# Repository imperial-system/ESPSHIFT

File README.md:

# ESP8266 8 RELAY
 ESPSHIFT es una placa DIY diseñada para el Internet Of Things, cuenta con 8 relays y fuente de alimentación propia. Esta basado en el ESP01 que resulta barato y facil para removerlo y programarlo de forma externa. 
 El proyecto esta realizado en kicad

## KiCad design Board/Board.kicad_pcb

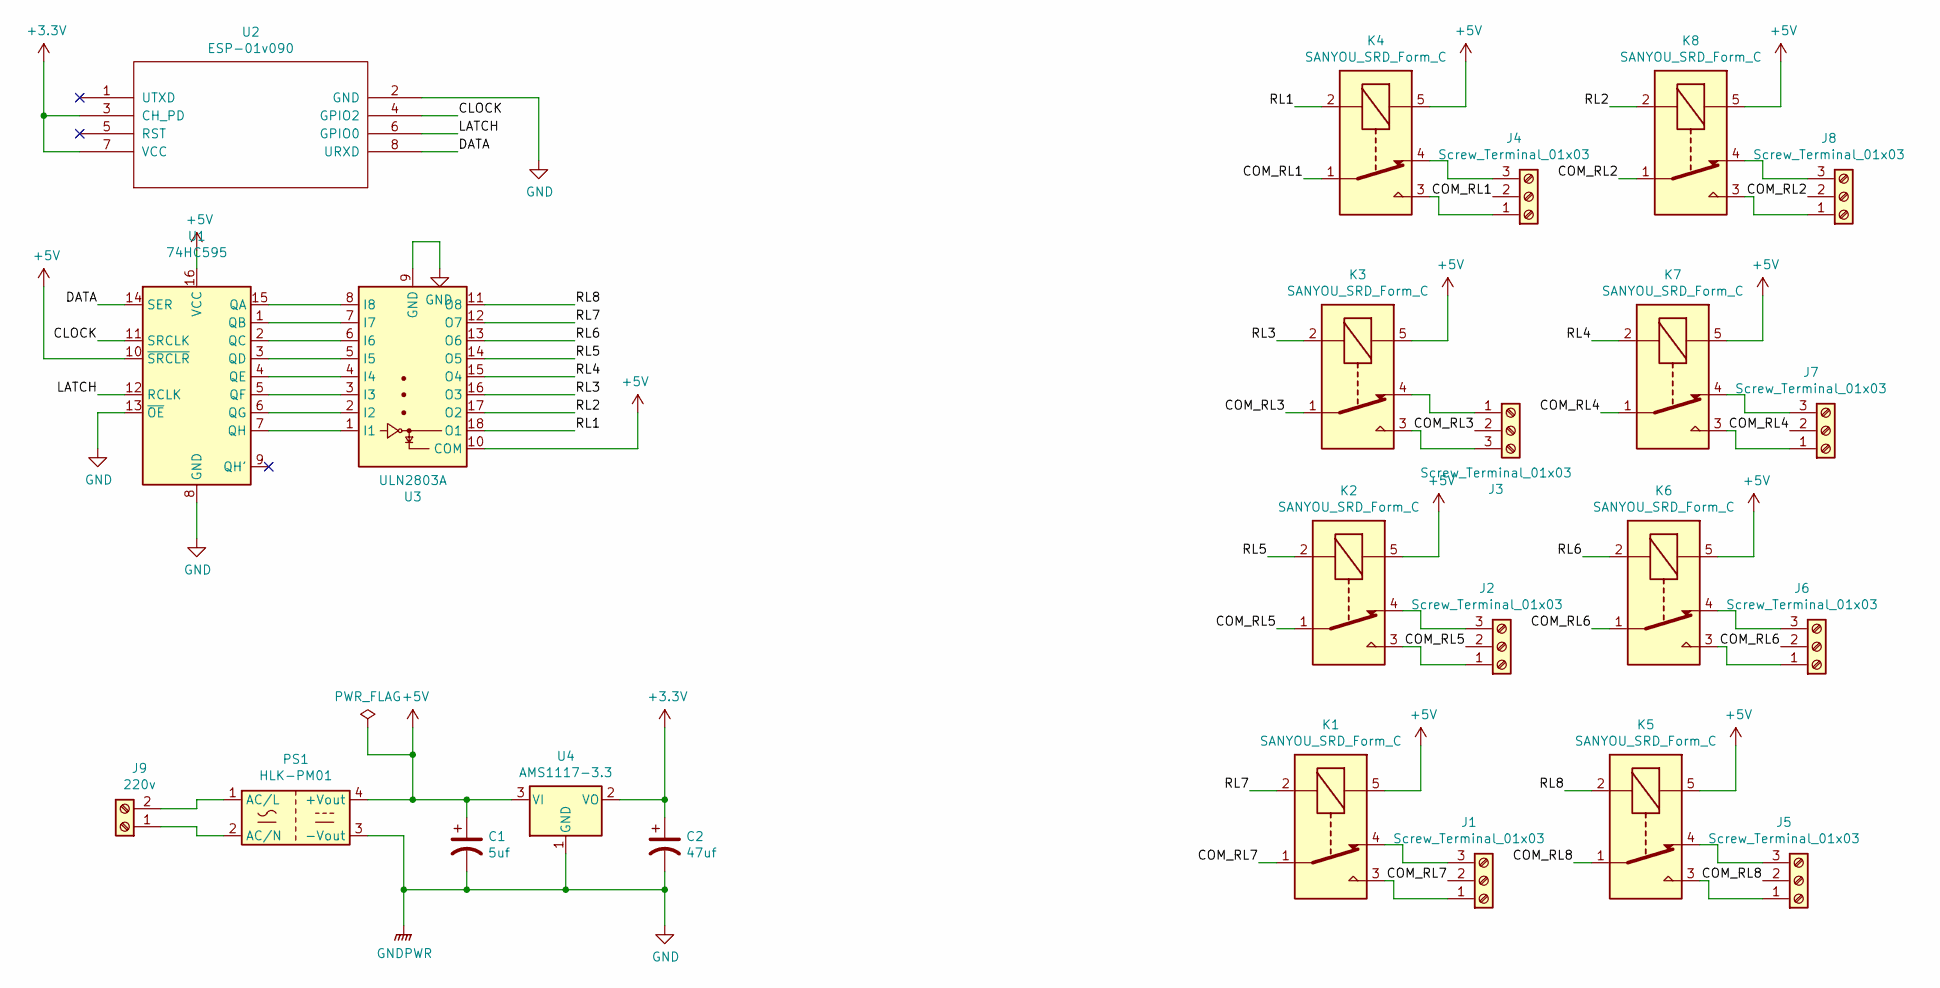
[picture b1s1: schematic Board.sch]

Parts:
C1: 5uf; CP_Radial_D4.0mm_P1.50mm
C2: 47uf; CP_Radial_D4.0mm_P1.50mm
J1, J2, J3, J4, J5, J6, J7, J8: Screw_Terminal_01x03; TerminalBlock_bornier-3_P5.08mm
J9: 220v; TerminalBlock_Altech_AK300-2_P5.00mm
K1, K2, K3, K4, K5, K6, K7, K8: SANYOU_SRD_Form_C; Relay_SPDT_SANYOU_SRD_Series_Form_C
PS1: HLK-PM01; Converter_ACDC_HiLink_HLK-PMxx
U1: 74HC595; DIP-16_W7.62mm_LongPads
U2: ESP-01v090; ESP-01
U3: ULN2803A; DIP-18_W7.62mm_LongPads
U4: AMS1117-3.3; SOT-23_Handsoldering

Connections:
+3V3: C2.1, U2.3 (CH_PD), U2.7 (VCC), U4.2 (VO)
+5V: C1.1, K1.5, K2.5, K3.5, K4.5, K5.5, K6.5, K7.5, K8.5, PS1.4 (+Vout), U1.10 (~SRCLR), U1.16 (VCC), U3.10 (COM), U4.3 (VI)
/CLOCK: U1.11 (SRCLK), U2.4 (GPIO2)
/COM_RL1: J4.2, K4.1
/COM_RL2: J8.2, K8.1
/COM_RL3: J3.2, K3.1
/COM_RL4: J7.2, K7.1
/COM_RL5: J2.2, K2.1
/COM_RL6: J6.2, K6.1
/COM_RL7: J1.2, K1.1
/COM_RL8: J5.2, K5.1
/DATA: U1.14 (SER), U2.8 (URXD)
/LATCH: U1.12 (RCLK), U2.6 (GPIO0)
/RL1: K4.2, U3.18 (O1)
/RL2: K8.2, U3.17 (O2)
/RL3: K3.2, U3.16 (O3)
/RL4: K7.2, U3.15 (O4)
/RL5: K2.2, U3.14 (O5)
/RL6: K6.2, U3.13 (O6)
/RL7: K1.2, U3.12 (O7)
/RL8: K5.2, U3.11 (O8)
GND: C1.2, C2.2, PS1.3 (-Vout), U1.8 (GND), U1.13 (~OE), U2.2 (GND), U3.9 (GND), U4.1 (GND)
unnamed: J1.1, K1.3
unnamed: J1.3, K1.4
unnamed: J2.1, K2.3
unnamed: J2.3, K2.4
unnamed: J3.1, K3.4
unnamed: J3.3, K3.3
unnamed: J4.1, K4.3
unnamed: J4.3, K4.4
unnamed: J5.1, K5.3
unnamed: J5.3, K5.4
unnamed: J6.1, K6.3
unnamed: J6.3, K6.4
unnamed: J7.1, K7.3
unnamed: J7.3, K7.4
unnamed: J8.1, K8.3
unnamed: J8.3, K8.4
unnamed: J9.1, PS1.2 (AC/N)
unnamed: J9.2, PS1.1 (AC/L)
unnamed: U1.1 (QB), U3.7 (I7)
unnamed: U1.2 (QC), U3.6 (I6)
unnamed: U1.3 (QD), U3.5 (I5)
unnamed: U1.4 (QE), U3.4 (I4)
unnamed: U1.5 (QF), U3.3 (I3)
unnamed: U1.6 (QG), U3.2 (I2)
unnamed: U1.7 (QH), U3.1 (I1)
unnamed: U1.15 (QA), U3.8 (I8)

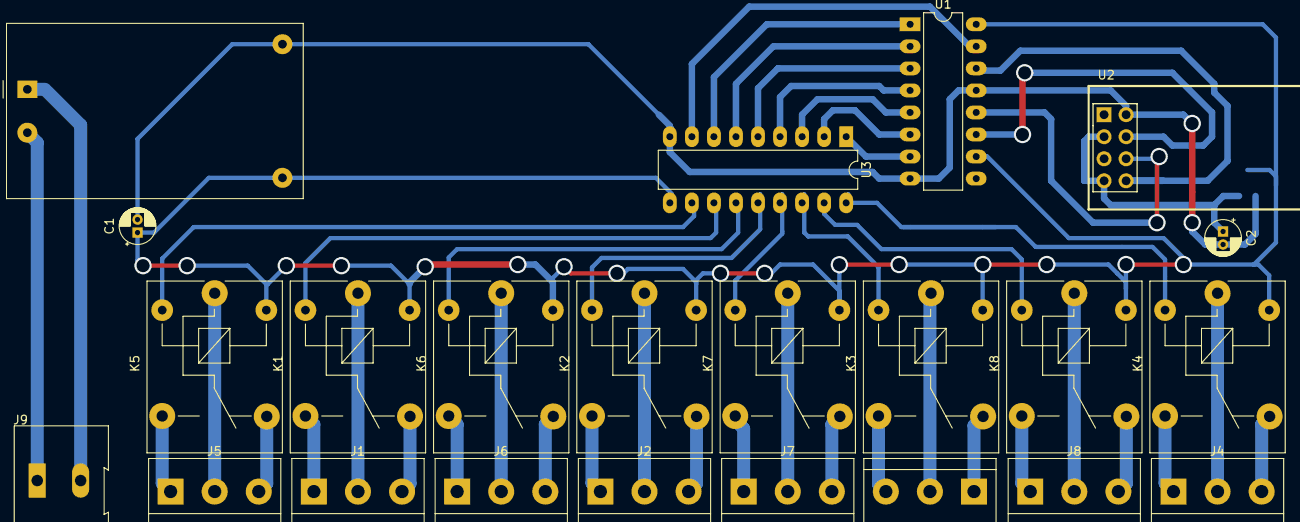
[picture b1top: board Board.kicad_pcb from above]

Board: 2 copper layers, 24 parts (1 on the bottom side), 48 nets.

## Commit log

2019-11-04 Finished circuit dessign and footprtints, starting with pcb
2019-11-06 Finished PCB
2019-11-06 Starting code, still a work in process
